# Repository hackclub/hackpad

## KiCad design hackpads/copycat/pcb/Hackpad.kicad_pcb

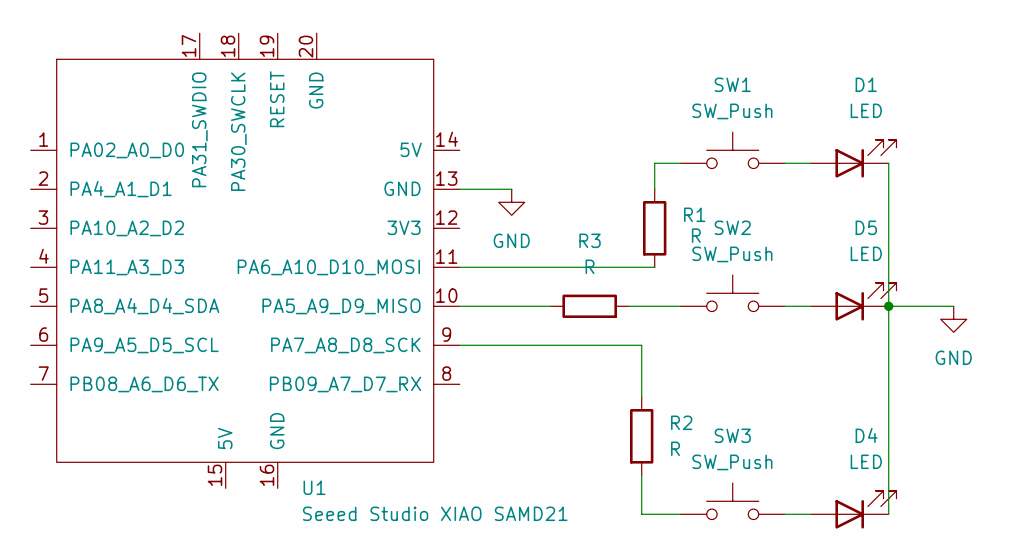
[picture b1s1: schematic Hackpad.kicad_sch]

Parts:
D1, D4, D5: LED; LED_D1.8mm_W1.8mm_H2.4mm_Horizontal_O1.27mm_Z8.2mm
R1, R2, R3: R; R_Axial_DIN0207_L6.3mm_D2.5mm_P7.62mm_Horizontal
SW1, SW2, SW3: SW_Push; SW_Cherry_MX_1.00u_PCB
U1: Seeed Studio XIAO SAMD21; XIAO-Generic-Hybrid-14P-2.54-21X17.8MM

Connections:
GND: D1.1 (K), D4.1 (K), D5.1 (K), U1.13 (GND)
unnamed: D1.2 (A), SW1.2
unnamed: D4.2 (A), SW3.2
unnamed: D5.2 (A), SW2.2
unnamed: R1.1, SW1.1
unnamed: R2.2, SW3.1
unnamed: R3.2, SW2.1
unnamed: R3.1, U1.10 (PA5_A9_D9_MISO)
unnamed: R1.2, U1.11 (PA6_A10_D10_MOSI)
unnamed: R2.1, U1.9 (PA7_A8_D8_SCK)

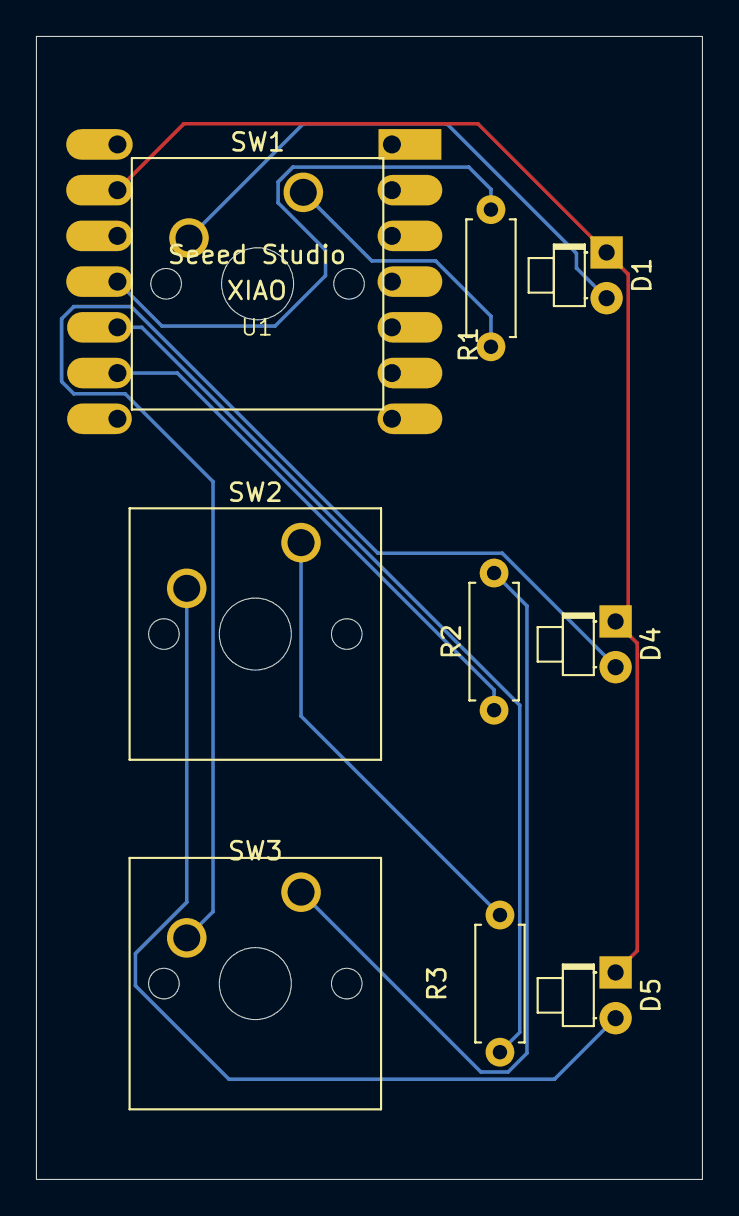
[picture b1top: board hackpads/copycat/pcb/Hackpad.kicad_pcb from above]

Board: 2 copper layers, 37.0 x 63.5 mm, 10 parts (1 on the bottom side), 10 nets.

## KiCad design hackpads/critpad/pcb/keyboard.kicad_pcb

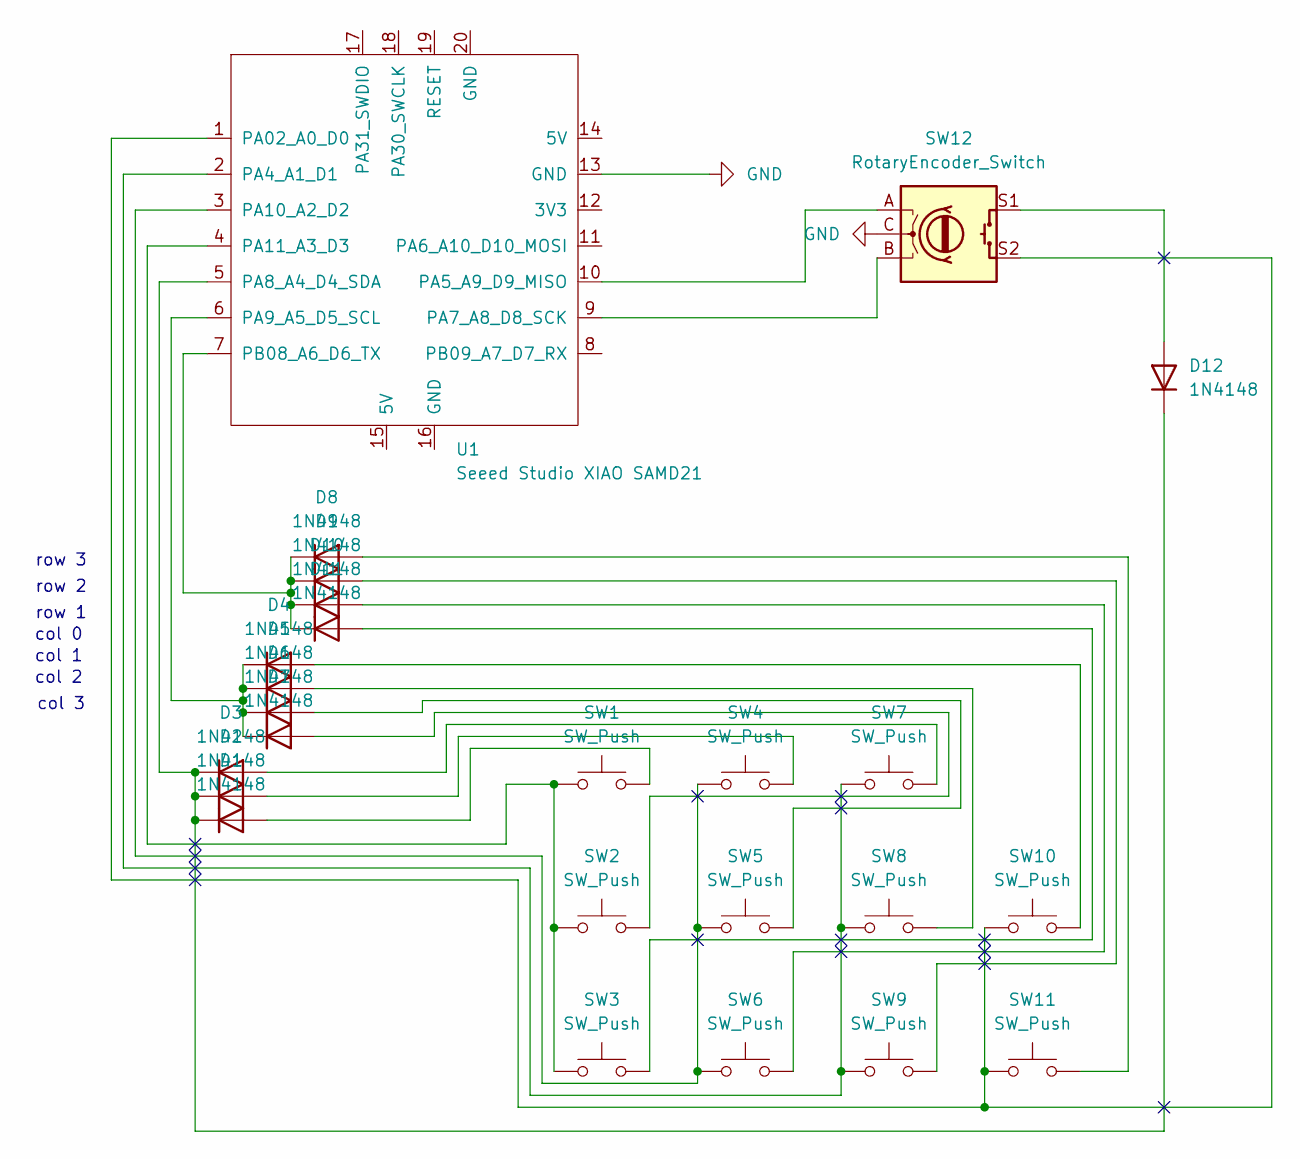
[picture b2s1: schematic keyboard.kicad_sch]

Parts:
D1, D2, D3, D4, D5, D6, D7, D8, D9, D10, D11, D12: 1N4148; D_DO-35_SOD27_P7.62mm_Horizontal
SW1, SW2, SW3, SW4, SW5, SW6, SW7, SW8, SW9, SW10, SW11: SW_Push; SW_Cherry_MX_1.00u_PCB
SW12: RotaryEncoder_Switch; RotaryEncoder_Alps_EC11E-Switch_Vertical_H20mm
U1: Seeed Studio XIAO SAMD21; MOUDLE14P-2.54-21X17.8MM

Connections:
GND: SW12.C, U1.13 (GND)
unnamed: D1.2 (A), SW1.2
unnamed: D1.1 (K), D2.1 (K), D3.1 (K), D12.1 (K), U1.5 (PA8_A4_D4_SDA)
unnamed: D2.2 (A), SW4.2
unnamed: D3.2 (A), SW7.2
unnamed: D4.2 (A), SW10.2
unnamed: D4.1 (K), D5.1 (K), D6.1 (K), D7.1 (K), U1.6 (PA9_A5_D5_SCL)
unnamed: D5.2 (A), SW8.2
unnamed: D6.2 (A), SW5.2
unnamed: D7.2 (A), SW2.2
unnamed: D8.2 (A), SW11.2
unnamed: D9.2 (A), SW9.2
unnamed: D10.2 (A), SW6.2
unnamed: D8.1 (K), D9.1 (K), D10.1 (K), D11.1 (K), U1.7 (PB08_A6_D6_TX)
unnamed: D11.2 (A), SW3.2
unnamed: D12.2 (A), SW12.S1
unnamed: SW10.1, SW11.1, SW12.S2, U1.1 (PA02_A0_D0)
unnamed: SW7.1, SW8.1, SW9.1, U1.2 (PA4_A1_D1)
unnamed: SW12.A, U1.10 (PA5_A9_D9_MISO)
unnamed: SW12.B, U1.9 (PA7_A8_D8_SCK)
unnamed: SW4.1, SW5.1, SW6.1, U1.3 (PA10_A2_D2)
unnamed: SW1.1, SW2.1, SW3.1, U1.4 (PA11_A3_D3)

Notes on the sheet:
row 1
row 3
col 3
col 1
col 2
col 0
row 2

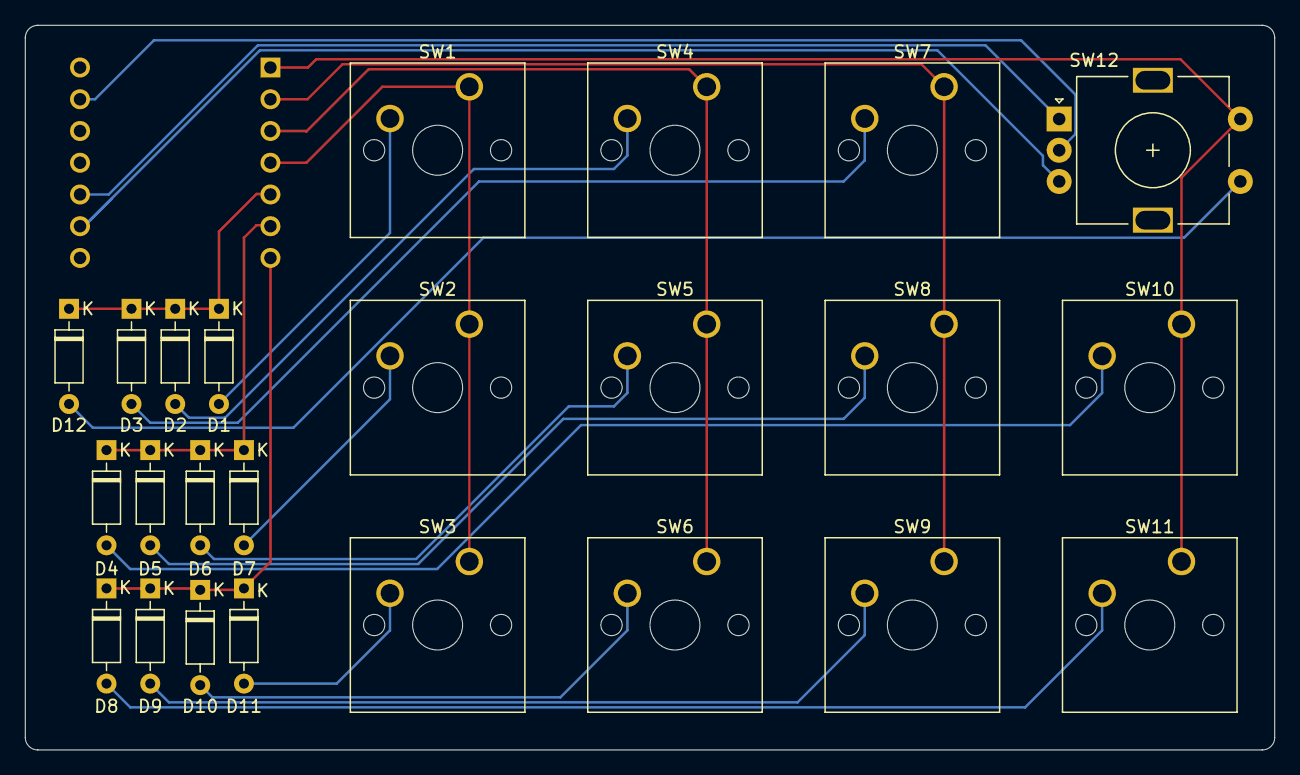
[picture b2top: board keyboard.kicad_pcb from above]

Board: 2 copper layers, 100.0 x 58.0 mm, 25 parts (1 on the bottom side), 22 nets.

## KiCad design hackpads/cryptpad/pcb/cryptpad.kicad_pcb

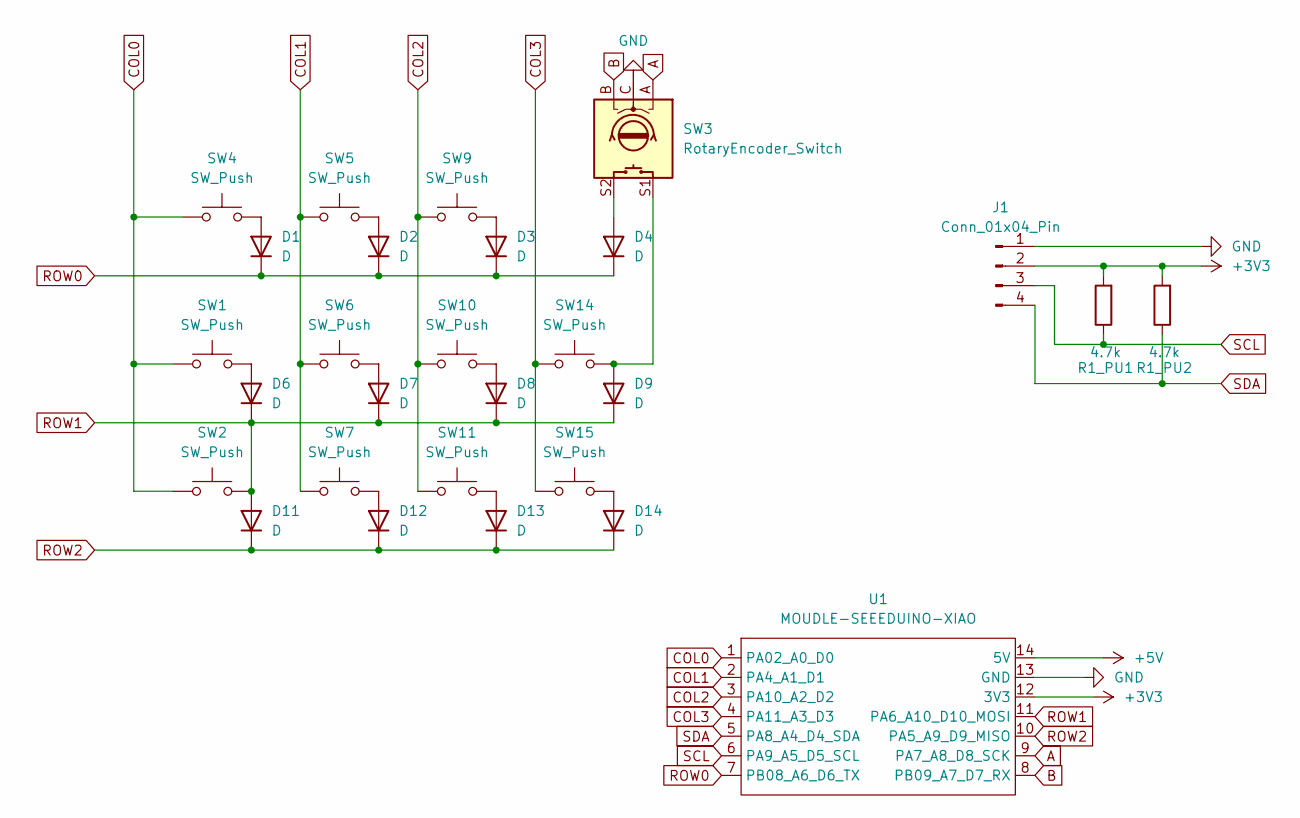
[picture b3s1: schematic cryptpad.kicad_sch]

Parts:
D1, D2, D3, D4, D6, D7, D8, D9, D11, D12, D13, D14: D; D_0805_2012Metric_Pad1.15x1.40mm_HandSolder
J1: Conn_01x04_Pin; MODULE_DM-OLED096-636
R1_PU1, R1_PU2: 4.7k; R_Axial_DIN0204_L3.6mm_D1.6mm_P7.62mm_Horizontal
SW1, SW2, SW4, SW5, SW6, SW7, SW9, SW10, SW11, SW14, SW15: SW_Push; SW_Cherry_MX_1.00u_PCB
SW3: RotaryEncoder_Switch; RotaryEncoder_Alps_EC11E-Switch_Vertical_H20mm
U1: MOUDLE-SEEEDUINO-XIAO; XIAO-Generic-Hybrid-14P-2.54-21X17.8MM

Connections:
+3V3: J1.2, R1_PU1.2, R1_PU2.2, U1.12 (3V3)
+5V: U1.14 (5V)
A: SW3.A, U1.9 (PA7_A8_D8_SCK)
B: SW3.B, U1.8 (PB09_A7_D7_RX)
COL0: SW1.1, SW2.1, SW4.1, U1.1 (PA02_A0_D0)
COL1: SW5.1, SW6.1, SW7.1, U1.2 (PA4_A1_D1)
COL2: SW9.1, SW10.1, SW11.1, U1.3 (PA10_A2_D2)
COL3: SW14.1, SW15.1, U1.4 (PA11_A3_D3)
GND: J1.1, SW3.C, U1.13 (GND)
unnamed: D1.2 (A), SW4.2
unnamed: D2.2 (A), SW5.2
unnamed: D3.2 (A), SW9.2
unnamed: D4.2 (A), SW3.S2
unnamed: D6.2 (A), SW1.2
unnamed: D7.2 (A), SW6.2
unnamed: D8.2 (A), SW10.2
unnamed: D9.2 (A), SW3.S1, SW14.2
unnamed: D12.2 (A), SW7.2
unnamed: D13.2 (A), SW11.2
unnamed: D14.2 (A), SW15.2
ROW0: D1.1 (K), D2.1 (K), D3.1 (K), D4.1 (K), U1.7 (PB08_A6_D6_TX)
ROW1: D6.1 (K), D7.1 (K), D8.1 (K), D9.1 (K), D11.2 (A), SW2.2, U1.11 (PA6_A10_D10_MOSI)
ROW2: D11.1 (K), D12.1 (K), D13.1 (K), D14.1 (K), U1.10 (PA5_A9_D9_MISO)
SCL: J1.3, R1_PU1.1, U1.6 (PA9_A5_D5_SCL)
SDA: J1.4, R1_PU2.1, U1.5 (PA8_A4_D4_SDA)

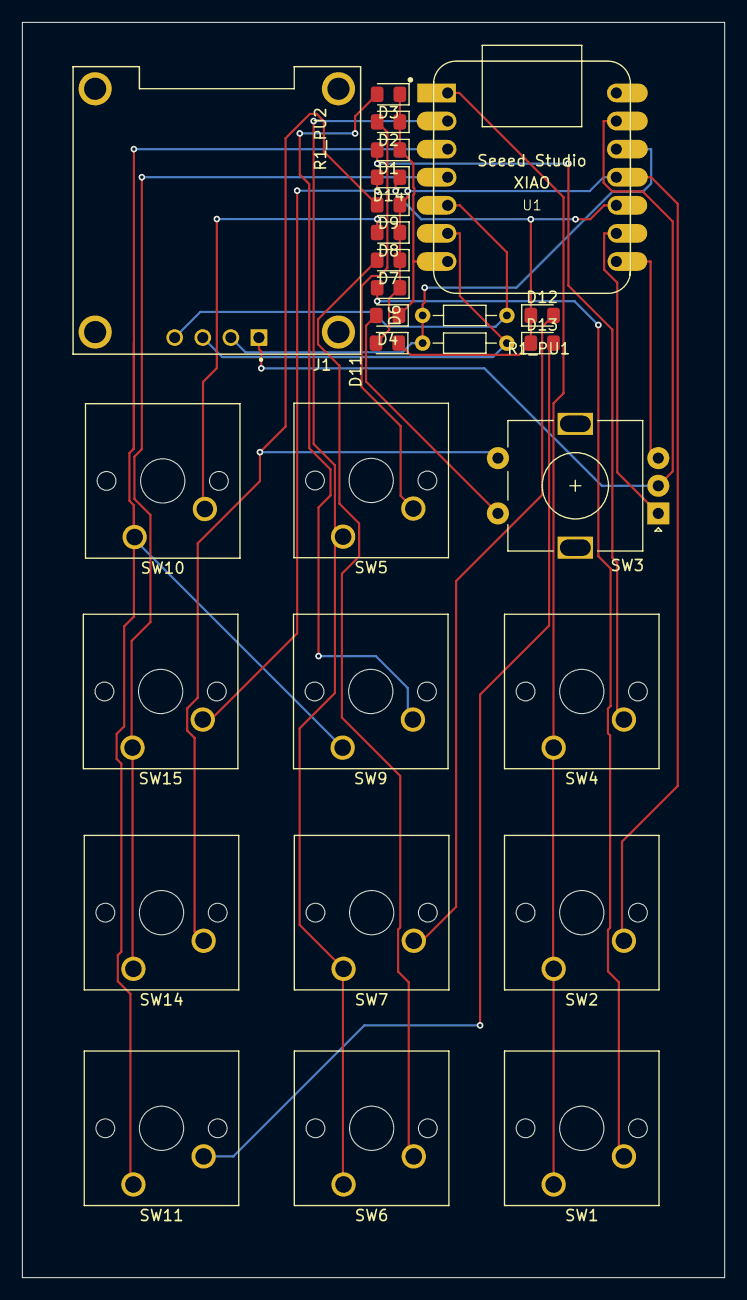
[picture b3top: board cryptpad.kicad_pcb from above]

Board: 2 copper layers, 63.5 x 113.5 mm, 28 parts (0 on the bottom side), 24 nets.

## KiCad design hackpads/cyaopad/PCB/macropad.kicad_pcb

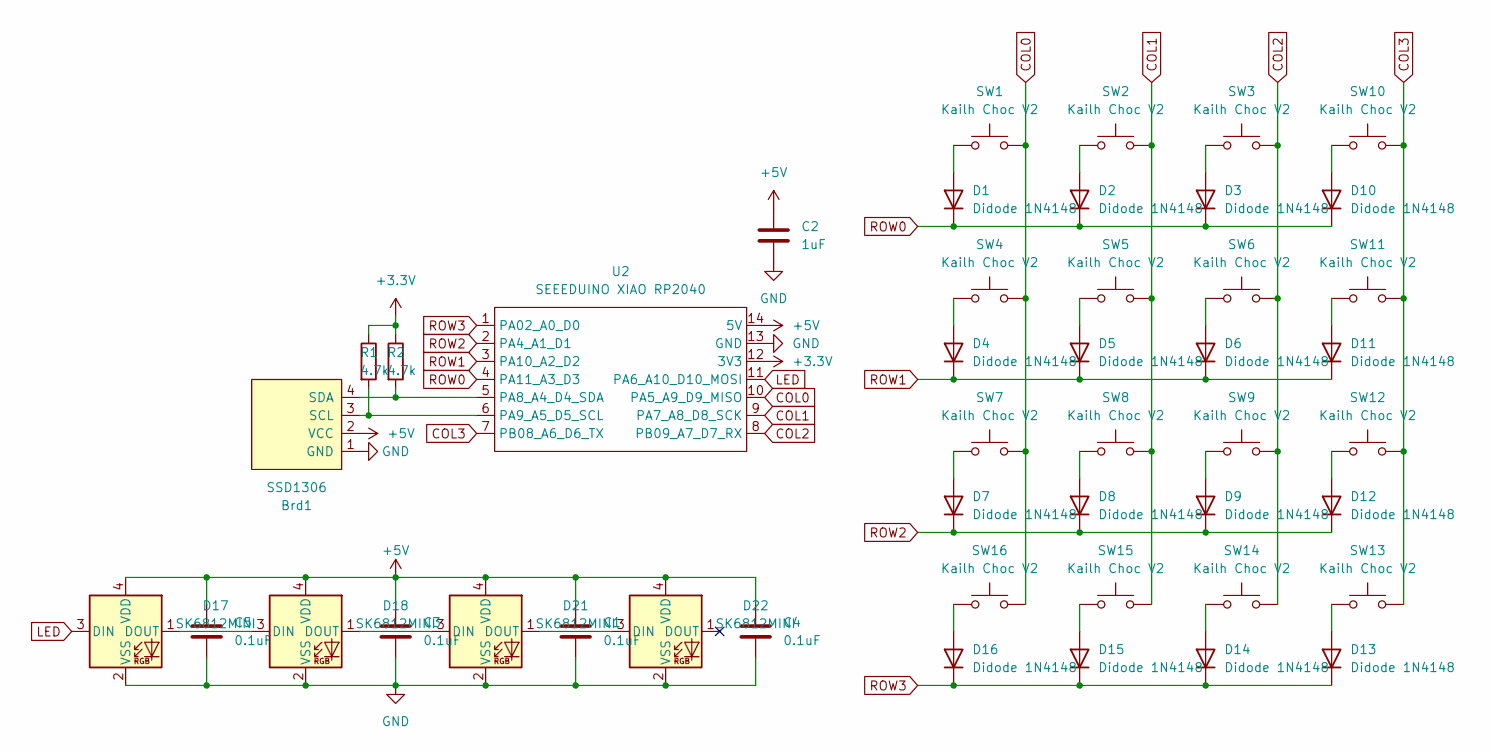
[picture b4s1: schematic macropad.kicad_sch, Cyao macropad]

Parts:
Brd1: SSD1306; 128x64OLED
C1, C3, C4, C5: 0.1uF; C_Disc_D3.0mm_W1.6mm_P2.50mm
C2: 1uF; C_Disc_D3.0mm_W1.6mm_P2.50mm
D1, D2, D3, D4, D5, D6, D7, D8, D9, D10, D11, D12, D13, D14, D15, D16: Didode 1N4148; D_DO-35_SOD27_P7.62mm_Horizontal
D17, D18, D21, D22: SK6812MINI; SK6812MINI-E
R1, R2: 4.7k; R_Axial_DIN0204_L3.6mm_D1.6mm_P7.62mm_Horizontal
SW1, SW2, SW3, SW4, SW5, SW6, SW7, SW8, SW9, SW10, SW11, SW12, SW13, SW14, SW15, SW16: Kailh Choc V2; SW_Kailh_Choc_V2_1.00u
U2: SEEEDUINO XIAO RP2040; XIAO-Generic-Hybrid-14P-2.54-21X17.8MM

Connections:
+3.3V: R1.1, R2.1, U2.12 (3V3)
+5V: Brd1.2 (VCC), C1.1, C2.1, C3.1, C4.1, C5.1, D17.4 (VDD), D18.4 (VDD), D21.4 (VDD), D22.4 (VDD), U2.14 (5V)
COL0: SW1.2, SW4.2, SW7.2, SW16.2, U2.10 (PA5_A9_D9_MISO)
COL1: SW2.2, SW5.2, SW8.2, SW15.2, U2.9 (PA7_A8_D8_SCK)
COL2: SW3.2, SW6.2, SW9.2, SW14.2, U2.8 (PB09_A7_D7_RX)
COL3: SW10.2, SW11.2, SW12.2, SW13.2, U2.7 (PB08_A6_D6_TX)
GND: Brd1.1 (GND), C1.2, C2.2, C3.2, C4.2, C5.2, D17.2 (VSS), D18.2 (VSS), D21.2 (VSS), D22.2 (VSS), U2.13 (GND)
LED: D17.3 (DIN), U2.11 (PA6_A10_D10_MOSI)
unnamed: Brd1.3 (SCL), R1.2, U2.6 (PA9_A5_D5_SCL)
unnamed: Brd1.4 (SDA), R2.2, U2.5 (PA8_A4_D4_SDA)
unnamed: D1.2 (A), SW1.1
unnamed: D2.2 (A), SW2.1
unnamed: D3.2 (A), SW3.1
unnamed: D4.2 (A), SW4.1
unnamed: D5.2 (A), SW5.1
unnamed: D6.2 (A), SW6.1
unnamed: D7.2 (A), SW7.1
unnamed: D8.2 (A), SW8.1
unnamed: D9.2 (A), SW9.1
unnamed: D10.2 (A), SW10.1
unnamed: D11.2 (A), SW11.1
unnamed: D12.2 (A), SW12.1
unnamed: D13.2 (A), SW13.1
unnamed: D14.2 (A), SW14.1
unnamed: D15.2 (A), SW15.1
unnamed: D16.2 (A), SW16.1
unnamed: D17.1 (DOUT), D18.3 (DIN)
unnamed: D18.1 (DOUT), D21.3 (DIN)
unnamed: D21.1 (DOUT), D22.3 (DIN)
ROW0: D1.1 (K), D2.1 (K), D3.1 (K), D10.1 (K), U2.4 (PA11_A3_D3)
ROW1: D4.1 (K), D5.1 (K), D6.1 (K), D11.1 (K), U2.3 (PA10_A2_D2)
ROW2: D7.1 (K), D8.1 (K), D9.1 (K), D12.1 (K), U2.2 (PA4_A1_D1)
ROW3: D13.1 (K), D14.1 (K), D15.1 (K), D16.1 (K), U2.1 (PA02_A0_D0)

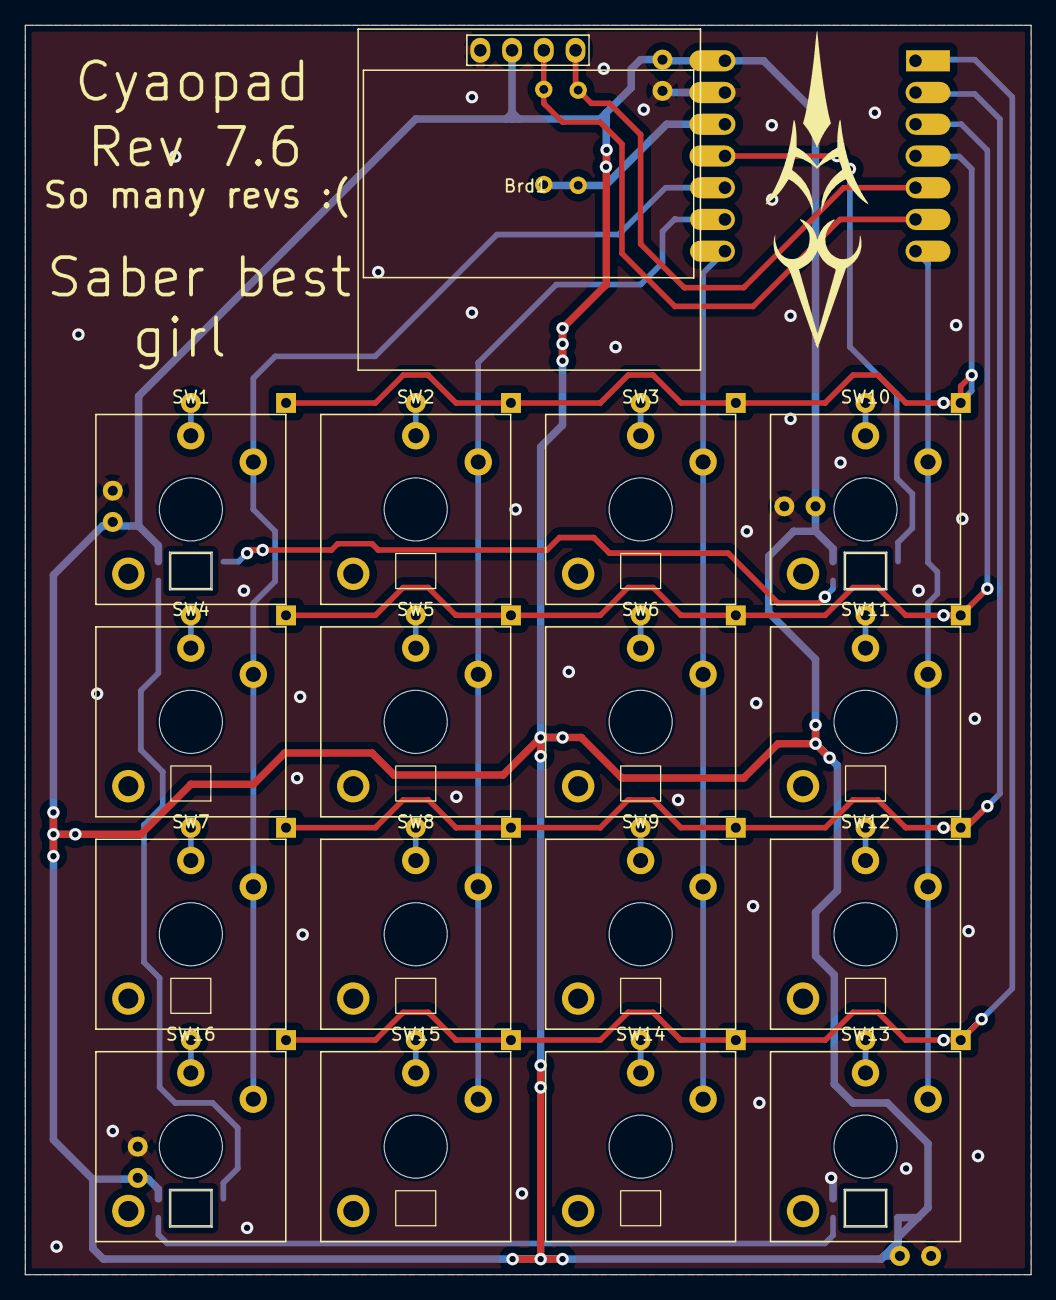
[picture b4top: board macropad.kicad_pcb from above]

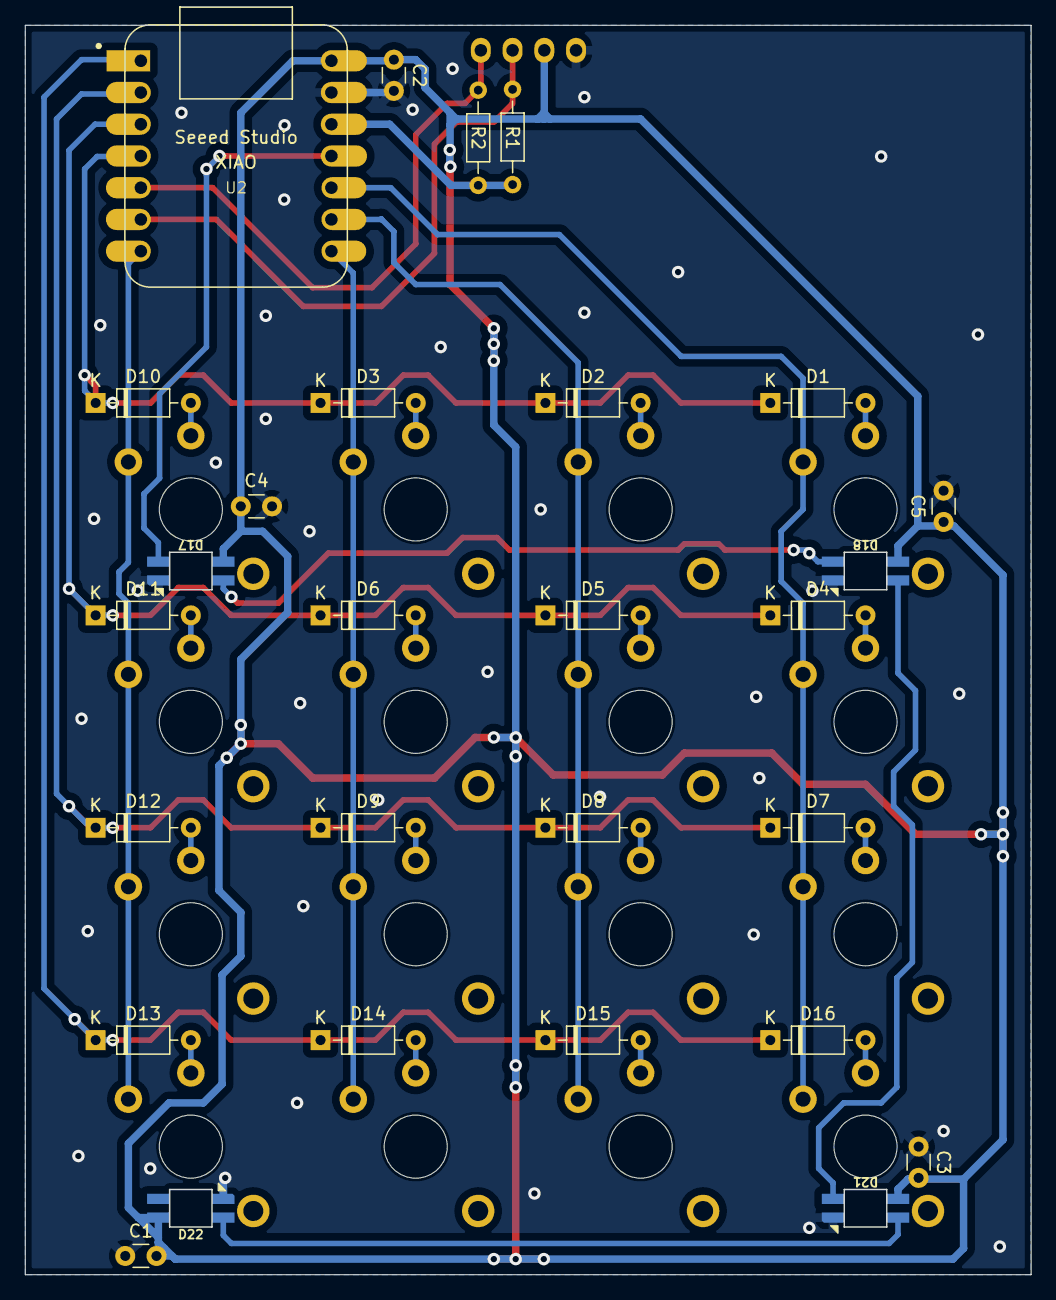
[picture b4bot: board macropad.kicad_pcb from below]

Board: 2 copper layers, 80.5 x 100.0 mm, 45 parts (28 on the bottom side), 33 nets.

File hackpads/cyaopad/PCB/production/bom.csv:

Designator,Footprint,Quantity,Value,LCSC Part #
BRD1,128x64OLED,1,SSD1306,
"C1, C3, C4, C5",C_Disc_D3.0mm_W1.6mm_P2.50mm,4,0.1uF,
C2,C_Disc_D3.0mm_W1.6mm_P2.50mm,1,1uF,
"D1, D10, D11, D12, D13, D14, D15, D16, D2, D3, D4, D5, D6, D7, D8, D9",D_DO-35_SOD27_P7.62mm_Horizontal,16,Didode 1N4148,
"D17, D18, D21, D22",SK6812MINI-E,4,SK6812MINI,
"R1, R2",R_Axial_DIN0204_L3.6mm_D1.6mm_P7.62mm_Horizontal,2,4.7k,
"SW1, SW10, SW11, SW12, SW13, SW14, SW15, SW16, SW2, SW3, SW4, SW5, SW6, SW7, SW8, SW9",SW_Kailh_Choc_V2_1.00u,16,Kailh Choc V2,
U2,XIAO-Generic-Hybrid-14P-2.54-21X17.8MM,1,SEEEDUINO XIAO RP2040,

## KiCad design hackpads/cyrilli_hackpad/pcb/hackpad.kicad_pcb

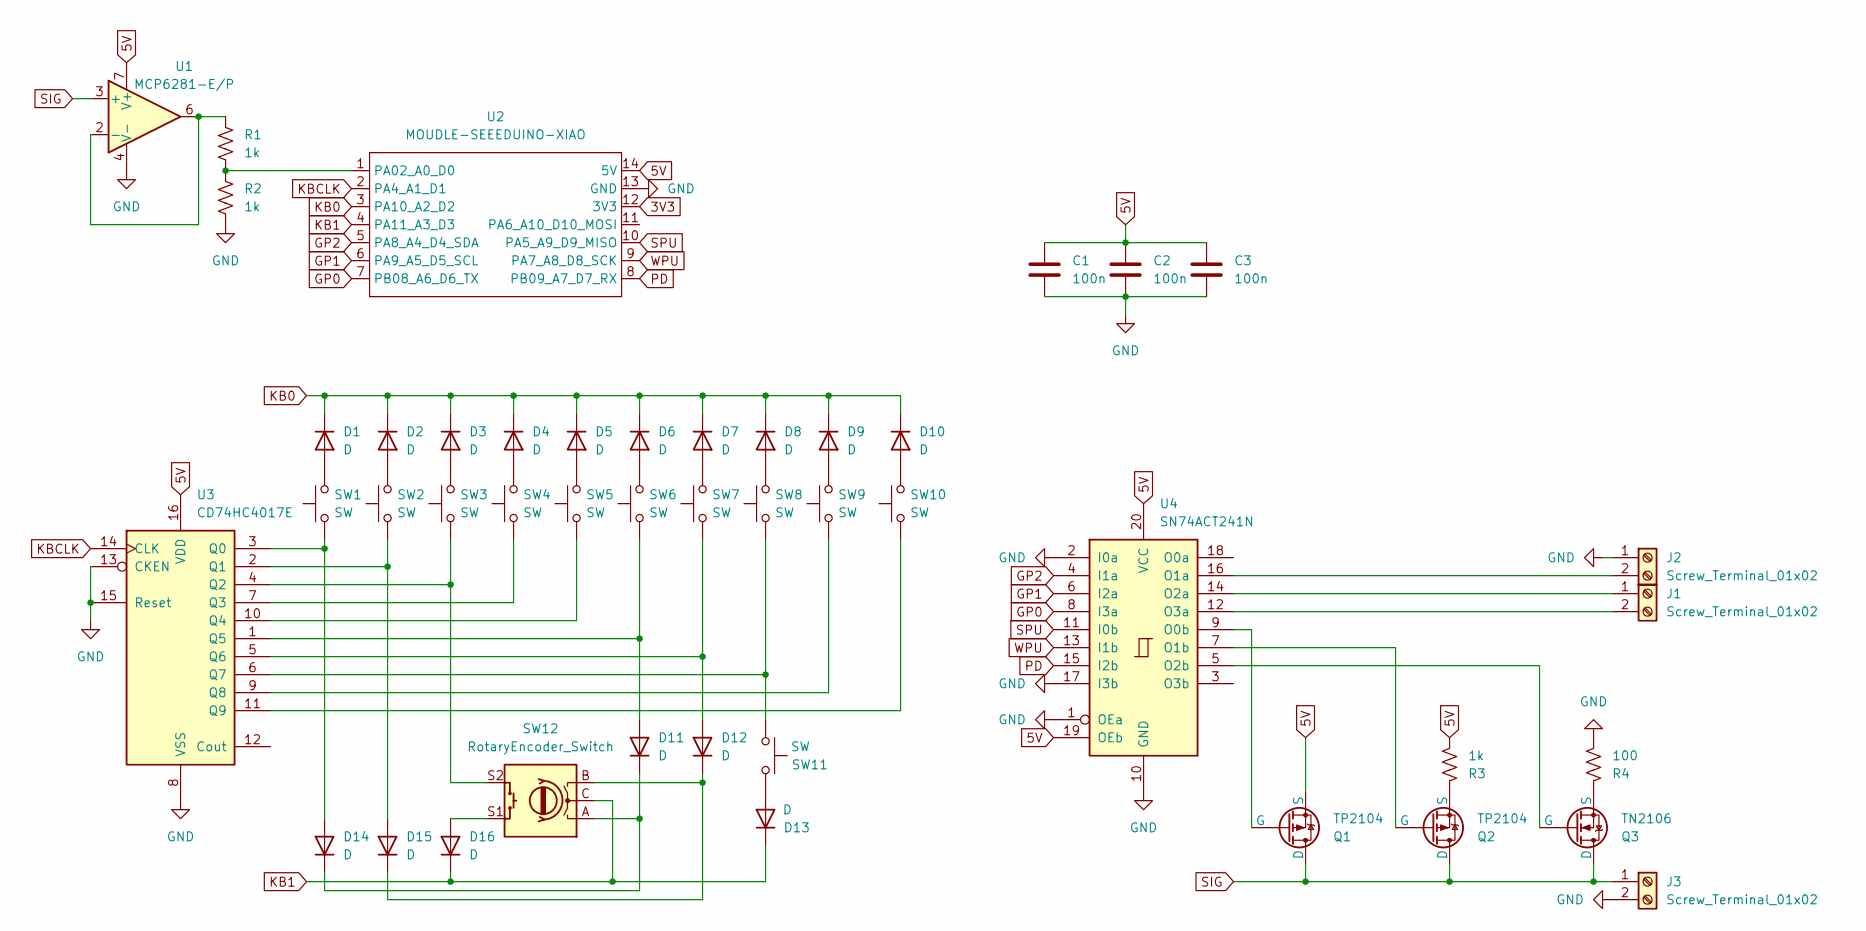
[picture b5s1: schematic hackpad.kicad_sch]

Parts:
C1, C2, C3: 100n; CAP_C320_KEM
D1, D2, D3, D4, D5, D6, D7, D8, D9, D10, D11, D12, D13, D14, D15, D16: D; D_DO-35_SOD27_P7.62mm_Horizontal
J1, J2, J3: Screw_Terminal_01x02; CONN2_710002_WRE
Q1, Q2: TP2104; TO-92_MC_MCH
Q3: TN2106; TO-92_MC_MCH
R1, R2, R3: 1k; R_Axial_DIN0207_L6.3mm_D2.5mm_P10.16mm_Horizontal
R4: 100; R_Axial_DIN0207_L6.3mm_D2.5mm_P10.16mm_Horizontal
SW1, SW2, SW3, SW4, SW5, SW6, SW7, SW8, SW9, SW10, SW11: SW; SW_Cherry_MX_1.00u_PCB
SW12: RotaryEncoder_Switch; RotaryEncoder_Alps_EC11E-Switch_Vertical_H20mm
U1: MCP6281-E/P; PDIP8_300MC_MCH
U2: MOUDLE-SEEEDUINO-XIAO; MOUDLE14P-2.54-21X17.8MM
U3: CD74HC4017E; N16
U4: SN74ACT241N; N20

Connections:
3V3: U2.12 (3V3)
5V: C1.1, C2.1, C3.1, Q1.1 (S), R3.2, U1.7 (V+), U2.14 (5V), U3.16 (VDD), U4.19 (OEb), U4.20 (VCC)
GND: C1.2, C2.2, C3.2, J2.1, J3.2, R2.2, R4.2, U1.4 (V-), U2.13 (GND), U3.8 (VSS), U3.13 (CKEN), U3.15 (Reset), U4.1 (OEa), U4.2 (I0a), U4.10 (GND), U4.17 (I3b)
GP0: U2.7 (PB08_A6_D6_TX), U4.8 (I3a)
GP1: U2.6 (PA9_A5_D5_SCL), U4.6 (I2a)
GP2: U2.5 (PA8_A4_D4_SDA), U4.4 (I1a)
KB0: D1.1 (K), D2.1 (K), D3.1 (K), D4.1 (K), D5.1 (K), D6.1 (K), D7.1 (K), D8.1 (K), D9.1 (K), D10.1 (K), U2.3 (PA10_A2_D2)
KB1: D13.1 (K), D16.1 (K), SW12.C, U2.4 (PA11_A3_D3)
KBCLK: U2.2 (PA4_A1_D1), U3.14 (CLK)
unnamed: D1.2 (A), SW1.2
unnamed: D2.2 (A), SW2.2
unnamed: D3.2 (A), SW3.2
unnamed: D4.2 (A), SW4.2
unnamed: D5.2 (A), SW5.2
unnamed: D6.2 (A), SW6.2
unnamed: D7.2 (A), SW7.2
unnamed: D8.2 (A), SW8.2
unnamed: D9.2 (A), SW9.2
unnamed: D10.2 (A), SW10.2
unnamed: D11.2 (A), SW6.1, U3.1 (Q5)
unnamed: D11.1 (K), D14.1 (K), SW12.A
unnamed: D12.2 (A), SW7.1, U3.5 (Q6)
unnamed: D12.1 (K), D15.1 (K), SW12.B
unnamed: D13.2 (A), SW11.2
unnamed: D14.2 (A), SW1.1, U3.3 (Q0)
unnamed: D15.2 (A), SW2.1, U3.2 (Q1)
unnamed: D16.2 (A), SW12.S1
unnamed: J1.1, U4.14 (O2a)
unnamed: J1.2, U4.12 (O3a)
unnamed: J2.2, U4.16 (O1a)
unnamed: Q1.2 (G), U4.9 (O0b)
unnamed: Q2.2 (G), U4.7 (O1b)
unnamed: Q2.1 (S), R3.1
unnamed: Q3.2 (G), U4.5 (O2b)
unnamed: Q3.1 (S), R4.1
unnamed: R1.1, U1.2 (-), U1.6
unnamed: R1.2, R2.1, U2.1 (PA02_A0_D0)
unnamed: SW3.1, SW12.S2, U3.4 (Q2)
unnamed: SW4.1, U3.7 (Q3)
unnamed: SW5.1, U3.10 (Q4)
unnamed: SW8.1, SW11.1, U3.6 (Q7)
unnamed: SW9.1, U3.9 (Q8)
unnamed: SW10.1, U3.11 (Q9)
PD: U2.8 (PB09_A7_D7_RX), U4.15 (I2b)
SIG: J3.1, Q1.3 (D), Q2.3 (D), Q3.3 (D), U1.3 (+)
SPU: U2.10 (PA5_A9_D9_MISO), U4.11 (I0b)
WPU: U2.9 (PA7_A8_D8_SCK), U4.13 (I1b)

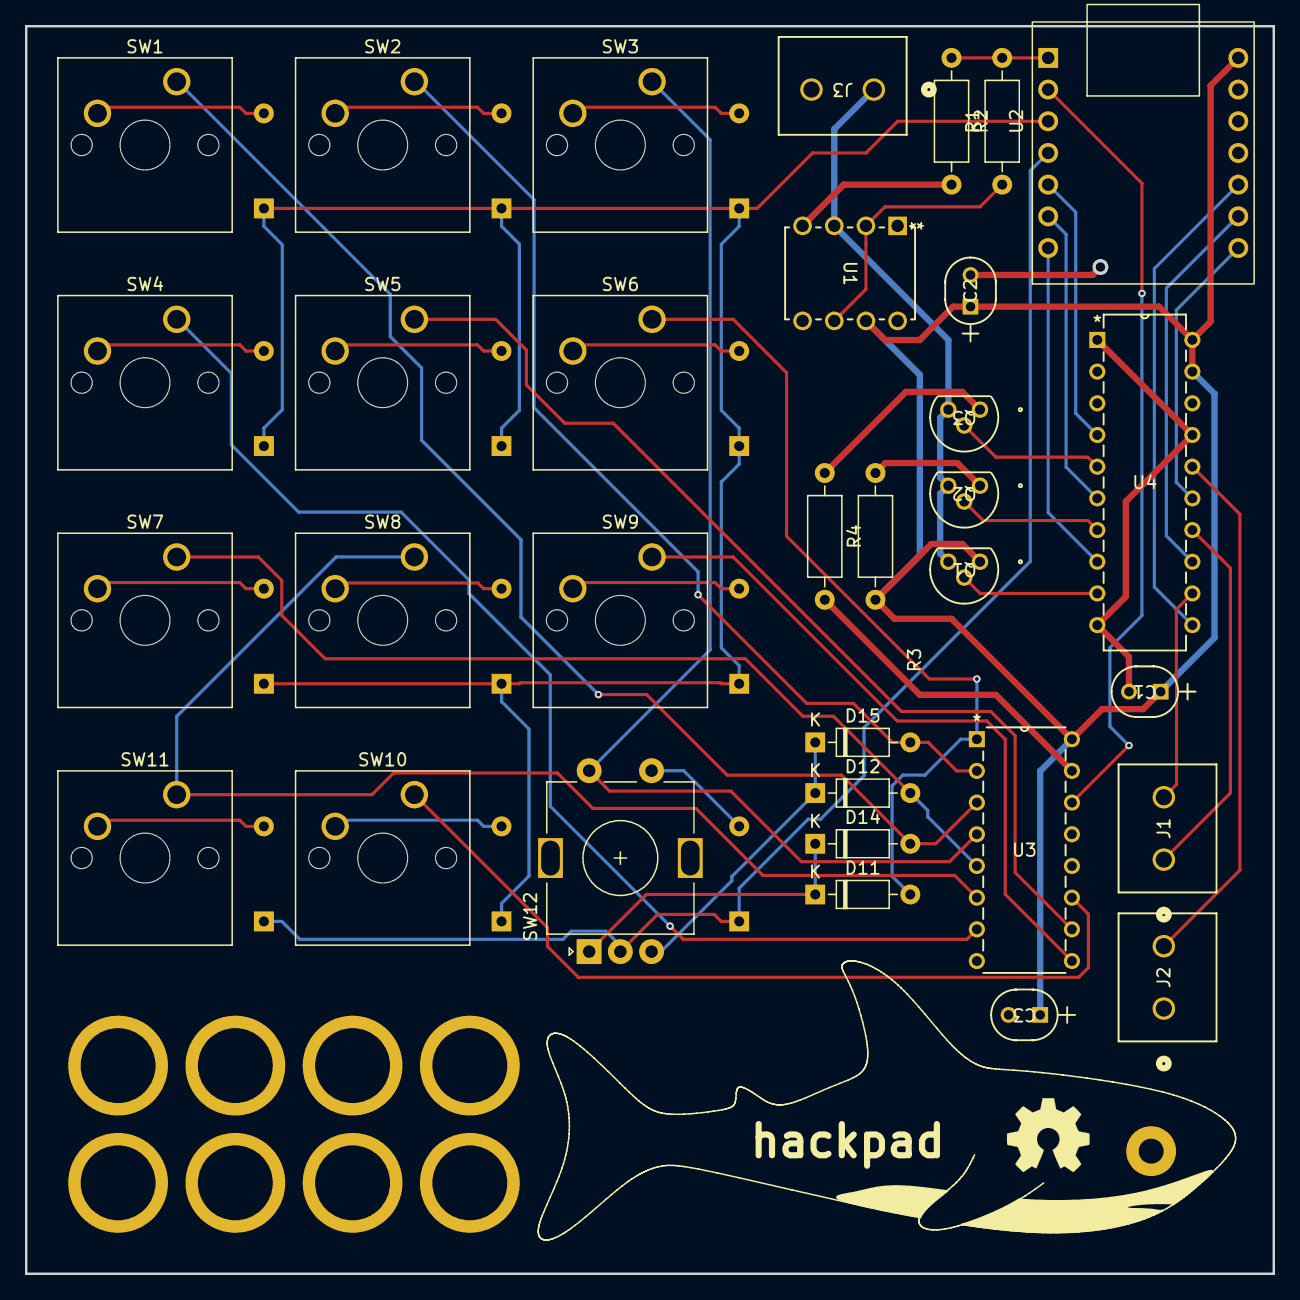
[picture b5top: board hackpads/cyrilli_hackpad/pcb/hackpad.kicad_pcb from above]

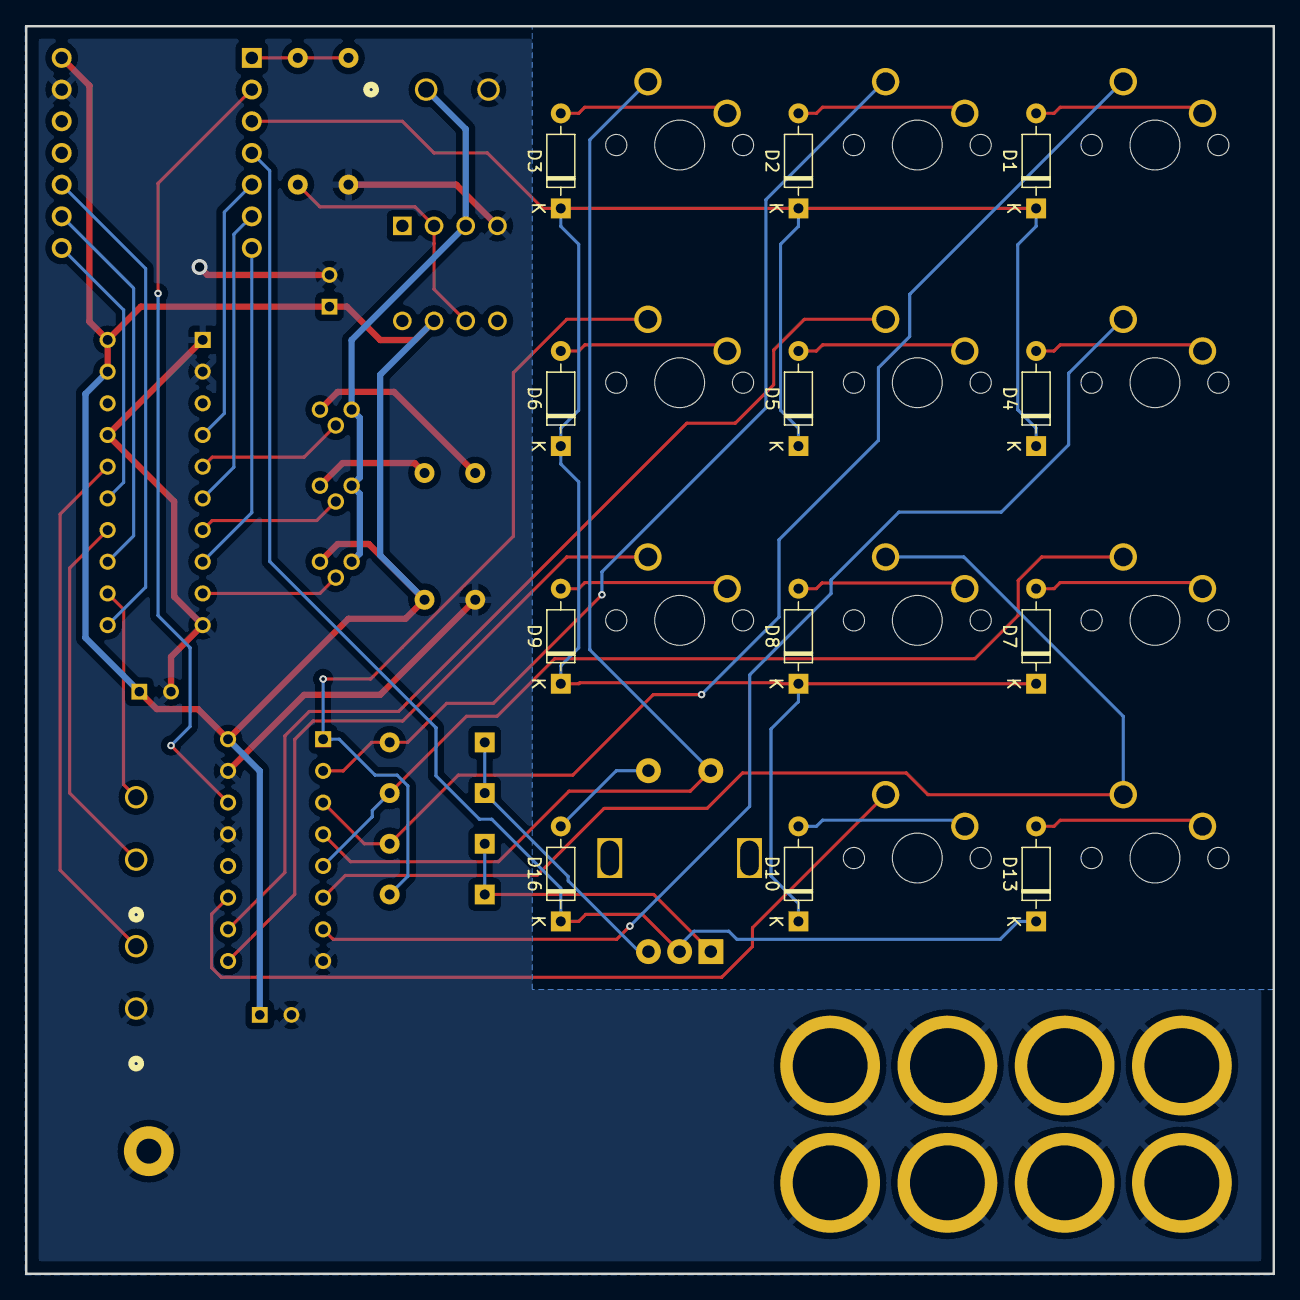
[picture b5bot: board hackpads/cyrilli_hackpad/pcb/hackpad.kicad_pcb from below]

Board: 2 copper layers, 100.0 x 100.0 mm, 45 parts (12 on the bottom side), 46 nets.
